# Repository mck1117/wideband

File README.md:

# rusEFI Wideband Controller

[User Documentation](https://rusefi.com/s/wb)

[Forum Thread](https://rusefi.com/forum/viewtopic.php?f=4&t=1856)

## Building Firmware

The `firmware/boards` directory contains configuration for each board this firmware supports.

For the standalone board and the module built in to rusEFI Hellen boards, `f0_module` is the correct target.  Use the `build_wideband.sh` script to build and package the wideband firmware: both a bin including the bootloader, and a header file consumed by rusEFI that contains no bootloader, to be uploaded over CAN (via the aforementioned bootloader).

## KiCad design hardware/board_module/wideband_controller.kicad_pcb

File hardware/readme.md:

* board_module
The main part of stm32f042 LSU 4.9 wideband.

* board_fw_tool
Initial USB DFU firmware programming fixture.

* board_carrier
Lower part of the sandwich.

* board_dev
Development version of above hardware.

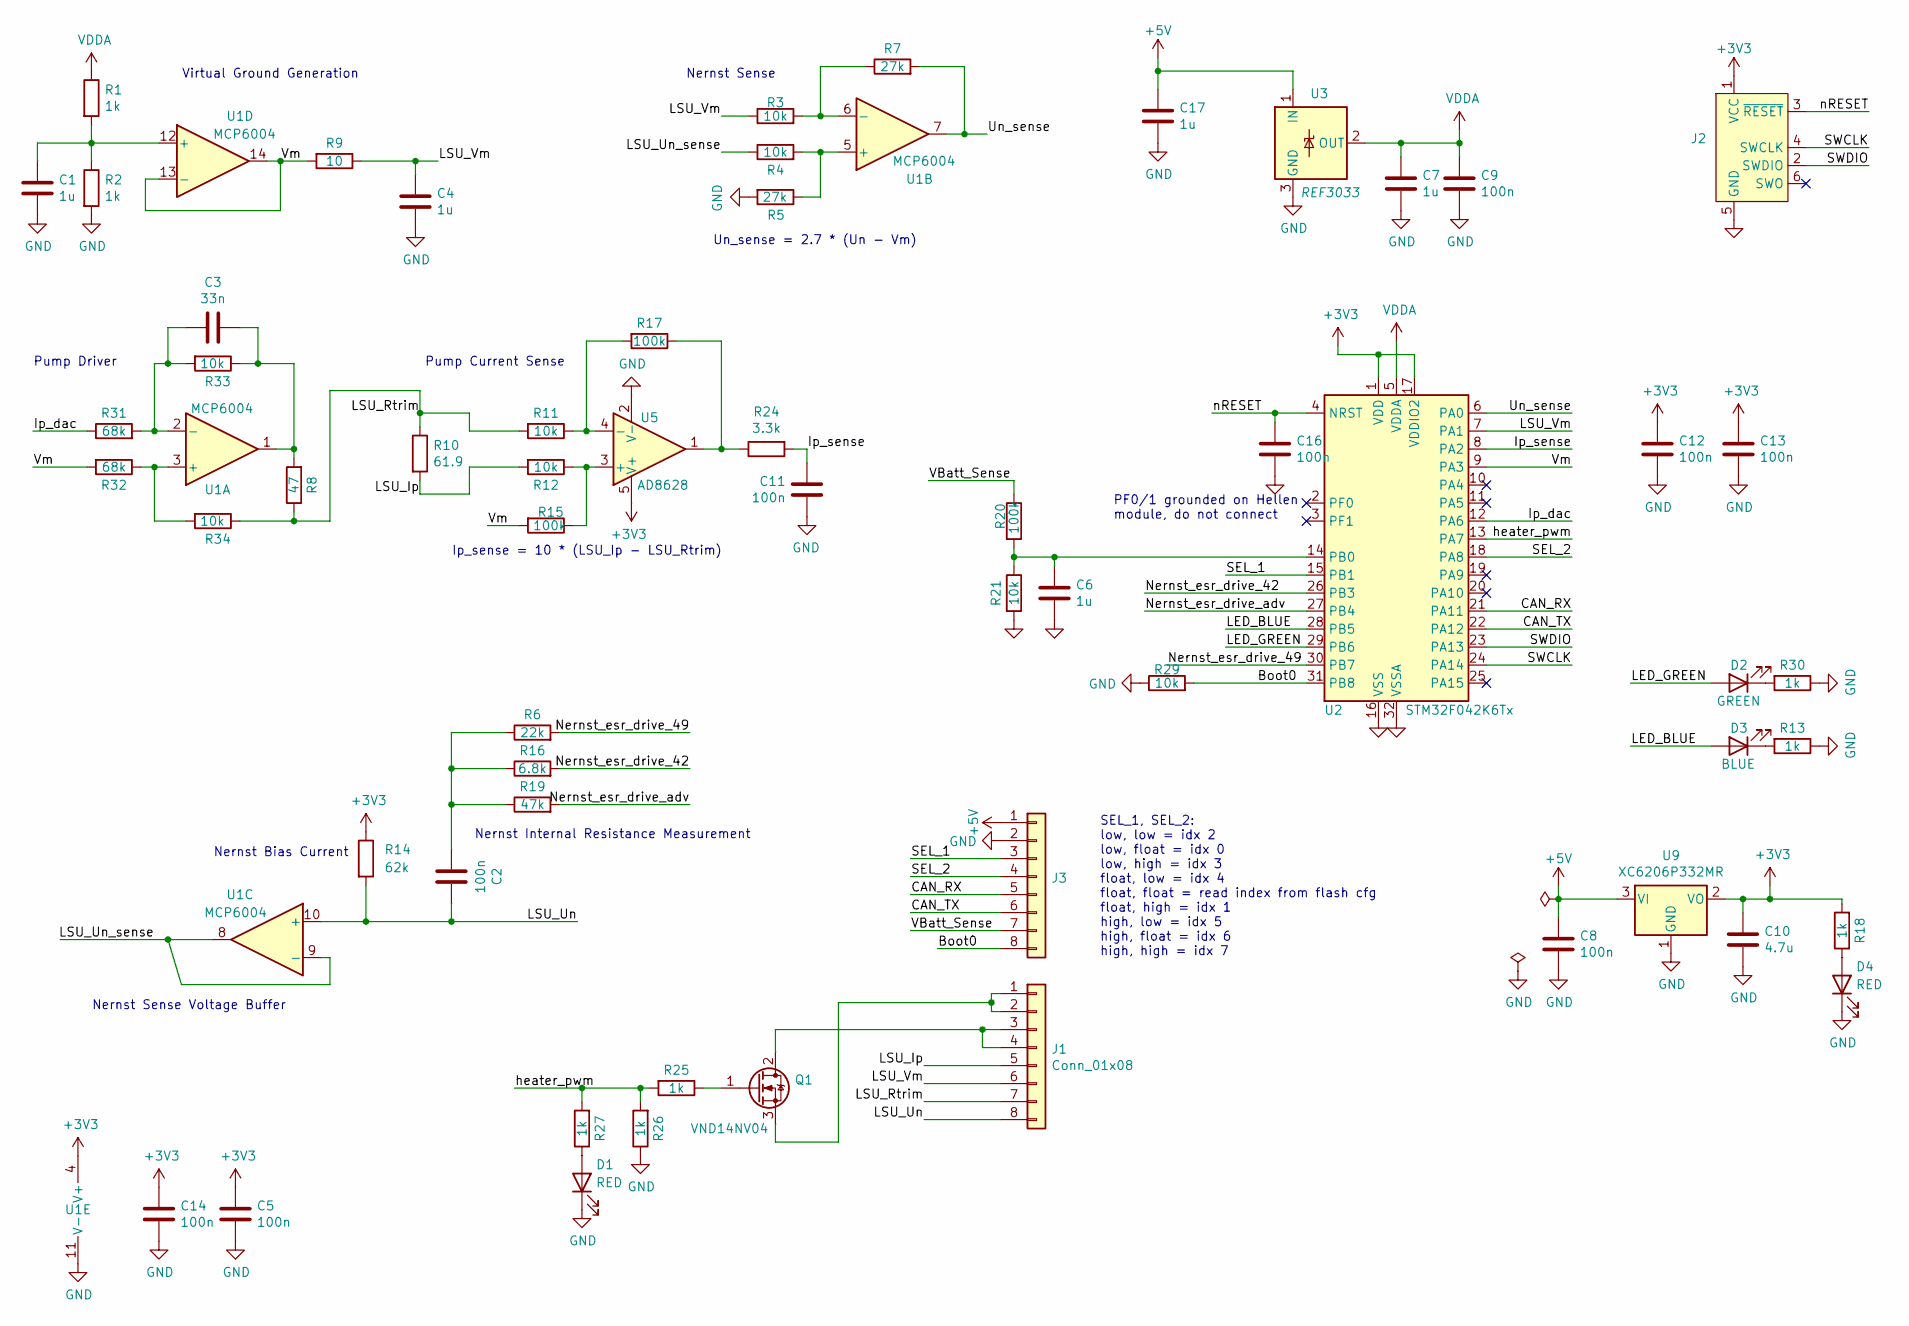
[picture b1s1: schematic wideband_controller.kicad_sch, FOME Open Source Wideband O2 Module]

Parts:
C1, C4, C6, C7, C17: 1u; C_0402_1005Metric; LCSC C52923
C2, C5, C8, C9, C11, C12, C13, C14, C16: 100n; C_0402_1005Metric; LCSC C1525
C3: 33n; C_0402_1005Metric; LCSC C1585
C10: 4.7u; C_0603_1608Metric; LCSC C19666
D1, D4: RED; LED_0603_1608Metric; LCSC C2286
D2: GREEN; LED_0603_1608Metric; LCSC C12624
D3: BLUE; LED_0603_1608Metric; LCSC C2288
J1, J3: Conn_01x08; PinHeader_1x08_P2.54mm_Vertical; LCSC C32713274
J2: Conn_ARM_SWD_TagConnect_TC2030; Tag-Connect_TC2030-IDC-NL_2x03_P1.27mm_Vertical
Q1: VND14NV04; TO-252-2; LCSC C2649436
R1, R2, R13, R18, R25, R26, R27, R30: 1k; R_0402_1005Metric; LCSC C11702
R3, R4, R11, R12, R21, R29, R33, R34: 10k; R_0402_1005Metric; LCSC C25744
R5, R7: 27k; R_0402_1005Metric; LCSC C25771
R6: 22k; R_0402_1005Metric; LCSC C25768
R8: 47; R_0402_1005Metric; LCSC C25118
R9: 10; R_0402_1005Metric; LCSC C25077
R10: 61.9; R_0603_1608Metric; LCSC C23092
R14: 62k; R_0603_1608Metric; LCSC C23221
R15, R17, R20: 100k; R_0402_1005Metric; LCSC C25741
R16: 6.8k; R_0402_1005Metric; LCSC C25917
R19: 47k; R_0402_1005Metric; LCSC C25792
R24: 3.3k; R_0402_1005Metric; LCSC C25890
R31, R32: 68k; R_0402_1005Metric; LCSC C36871
U1: MCP6004; TSSOP-14_4.4x5mm_P0.65mm; LCSC C50282
U2: STM32F042K6Tx; LQFP-32_7x7mm_P0.8mm; LCSC C69216
U3: REF3033; SOT-23; LCSC C36658
U5: AD8628; TSOT-23-5; LCSC C29309
U9: XC6206P332MR; SOT-23; LCSC C5446

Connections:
+3V3: C5.1, C10.1, C12.1, C13.1, C14.1, J2.1 (VCC), R14.1, R18.2, U1.4 (V+), U2.1 (VDD), U2.17 (VDDIO2), U5.5 (V+), U9.2 (VO)
+5V: C8.1, C17.1, J3.1, U3.1 (IN), U9.3 (VI)
/Boot0: J3.8, R29.2, U2.31 (PB8)
/CAN_RX: J3.5, U2.21 (PA11)
/CAN_TX: J3.6, U2.22 (PA12)
/Ip_dac: R31.1, U2.12 (PA6)
/Ip_sense: C11.1, R24.2, U2.8 (PA2)
/LED_BLUE: D3.2 (A), U2.28 (PB5)
/LED_GREEN: D2.2 (A), U2.29 (PB6)
/LSU_Ip: J1.5, R10.2, R12.2
/LSU_Rtrim: J1.7, R8.1, R10.1, R11.2, R34.1
/LSU_Un: C2.1, J1.8, R14.2, U1.10 (+)
/LSU_Un_sense: R4.1, U1.8, U1.9 (-)
/LSU_Vm: C4.1, J1.6, R3.1, R9.1, U2.7 (PA1)
/Nernst_esr_drive_42: R16.2, U2.26 (PB3)
/Nernst_esr_drive_49: R6.2, U2.30 (PB7)
/Nernst_esr_drive_adv: R19.2, U2.27 (PB4)
/SEL_1: J3.3, U2.15 (PB1)
/SEL_2: J3.4, U2.18 (PA8)
/SWCLK: J2.4 (SWCLK), U2.24 (PA14)
/SWDIO: J2.2 (SWDIO), U2.23 (PA13)
/Un_sense: R7.2, U1.7, U2.6 (PA0)
/VBatt_Sense: J3.7, R20.1
/Vm: R9.2, R15.2, R32.2, U1.13 (-), U1.14, U2.9 (PA3)
/heater_pwm: R25.2, R26.2, R27.2, U2.13 (PA7)
/nRESET: C16.1, J2.3 (~RESET), U2.4 (NRST)
GND: C1.2, C4.2, C5.2, C6.2, C7.2, C8.2, C9.2, C10.2, C11.2, C12.2, C13.2, C14.2, C16.2, C17.2, D1.1 (K), D4.1 (K), J2.5 (GND), J3.2, R2.2, R5.2, R13.1, R21.2, R26.1, R29.1, R30.1, U1.11 (V-), U2.16 (VSS), U2.32 (VSSA), U3.3 (GND), U5.2 (V-), U9.1 (GND)
unnamed: C2.2, R6.1, R16.1, R19.1
unnamed: C3.1, R8.2, R33.1, U1.1
unnamed: D1.2 (A), R27.1
unnamed: D2.1 (K), R30.2
unnamed: D3.1 (K), R13.2
unnamed: D4.2 (A), R18.1
unnamed: J1.1, J1.2, Q1.3 (S)
unnamed: J1.3, J1.4, Q1.2 (D)
unnamed: Q1.1 (G), R25.1
unnamed: R17.1, R24.1, U5.1
unnamed: R32.1, R34.2, U1.3 (+)
unnamed: C3.2, R31.2, R33.2, U1.2 (-)
unnamed: R4.2, R5.1, U1.5 (+)
unnamed: R3.2, R7.1, U1.6 (-)
unnamed: C1.1, R1.2, R2.1, U1.12 (+)
unnamed: C6.1, R20.2, R21.1, U2.14 (PB0)
unnamed: R12.1, R15.1, U5.3 (+)
unnamed: R11.1, R17.2, U5.4 (-)
VDDA: C7.1, C9.1, R1.1, U2.5 (VDDA), U3.2 (OUT)

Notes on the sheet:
Un_sense = 2.7 * (Un - Vm)
Nernst Internal Resistance Measurement
Pump Driver
Nernst Sense Voltage Buffer
PF0/1 grounded on Hellen module, do not connect
Nernst Bias Current
Ip_sense = 10 * (LSU_Ip - LSU_Rtrim)
Virtual Ground Generation
Nernst Sense
Pump Current Sense
SEL_1, SEL_2: low, low = idx 2 low, float = idx 0 low, high = idx 3 float, low = idx 4 float, float = read index from flash cfg float, high = idx 1 high, low = idx 5 high, float = idx 6 high, high = idx 7

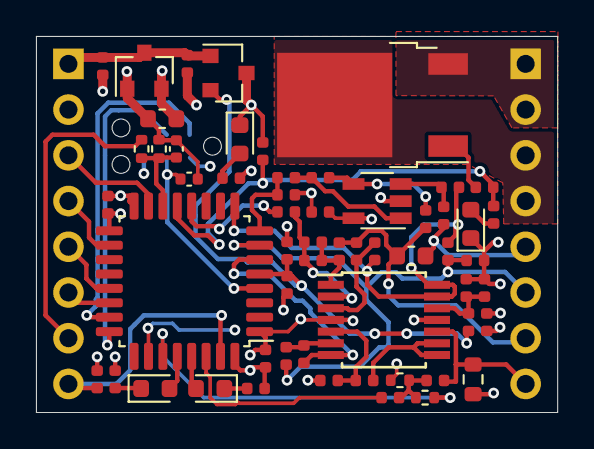
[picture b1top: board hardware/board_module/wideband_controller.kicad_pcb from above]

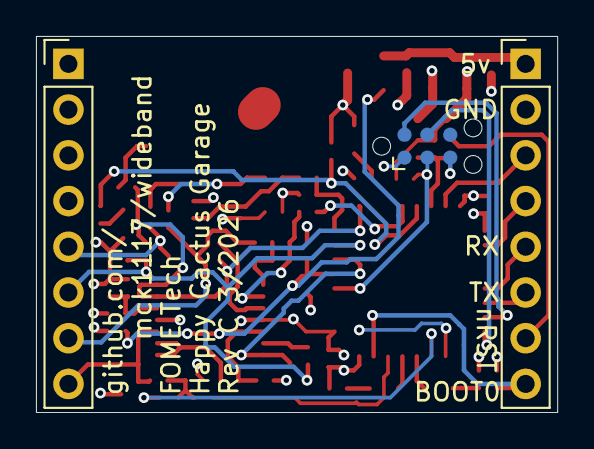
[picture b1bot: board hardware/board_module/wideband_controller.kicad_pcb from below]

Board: 4 copper layers, 29.0 x 20.9 mm, 60 parts (3 on the bottom side), 46 nets.

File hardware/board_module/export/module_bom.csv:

Comment,Designator,Footprint, LCSC
1u,"C1,C4,C7",Capacitor_SMD:C_0402_1005Metric,C52923
4.7u,C10,Capacitor_SMD:C_0603_1608Metric,C19666
100n,"C2,C8,C9,C11,C13,C12,C14,C5",Capacitor_SMD:C_0402_1005Metric,C1525
33n,C3,Capacitor_SMD:C_0402_1005Metric,C1585
DNP,"C6,C15",Capacitor_SMD:C_0402_1005Metric,
RED,"D1,D4",LED_SMD:LED_0603_1608Metric,C2286
GREEN,D2,LED_SMD:LED_0603_1608Metric,C72043
BLUE,D3,LED_SMD:LED_0603_1608Metric,C72041
BTS3028,Q1,Package_TO_SOT_SMD:TO-252-2,C112639
61.9,R10,Resistor_SMD:R_0603_1608Metric,C23092
100k,"R15,R17",Resistor_SMD:R_0402_1005Metric,C25741
10k,"R2,R11,R12,R4,R3,R1,R33,R34,R29",Resistor_SMD:R_0402_1005Metric,C25744
20k,"R22,R14,R16",Resistor_SMD:R_0402_1005Metric,C25765
33,R23,Resistor_SMD:R_0402_1005Metric,C25105
3.3k,R24,Resistor_SMD:R_0402_1005Metric,C25890
1k,"R25,R26,R27,R30,R13,R18",Resistor_SMD:R_0402_1005Metric,C11702
68k,"R32,R31",Resistor_SMD:R_0402_1005Metric,C36871
22k,R6,Resistor_SMD:R_0402_1005Metric,C25768
27k,"R7,R5",Resistor_SMD:R_0402_1005Metric,C25771
47,R8,Resistor_SMD:R_0402_1005Metric,C25118
10,R9,Resistor_SMD:R_0402_1005Metric,C25077
MCP6004,U1,Package_SO:TSSOP-14_4.4x5mm_P0.65mm,C50282
STM32F042K6Tx,U2,Package_QFP:LQFP-32_7x7mm_P0.8mm,C69216
AD8628,U5,Package_TO_SOT_SMD:TSOT-23-5,C29309
XC6206P332MR,U9,Package_TO_SOT_SMD:SOT-23,C5446

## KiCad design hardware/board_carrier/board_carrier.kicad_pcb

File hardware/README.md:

## `board_module`

Wideband O2 sensor controller on a postage stamp. Contains all the analog and digital control logic to handle a Bosch LSU 4.2, 4.9, or ADV sensor.

Intended to either be mounted on an ECU as a module, or on `board_carrier` to run standalone.

## `board_carrier`

Stacks under `board_module`, has 5v regulator, CAN tranceiver, etc so that the module can exist standlone.

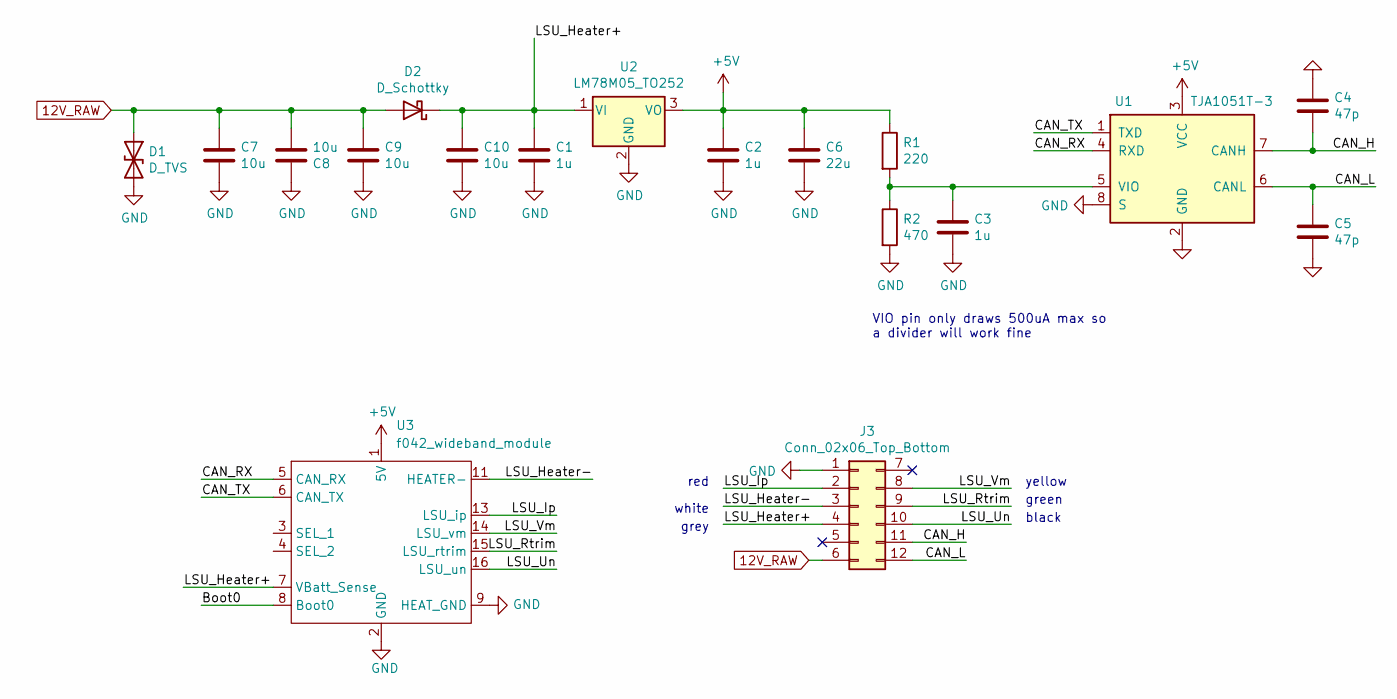
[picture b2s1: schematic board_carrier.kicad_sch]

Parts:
C1, C2, C3: 1u; C_0603_1608Metric; LCSC C15849
C4, C5: 47p; C_0402_1005Metric; LCSC C1567
C6: 22u; C_0805_2012Metric; LCSC C45783
C7, C8, C9, C10: 10u; C_1206_3216Metric; LCSC C13585
D1: D_TVS; D_SMC; LCSC C151279
D2: D_Schottky; D_SMA; LCSC C22452
J3: Conn_02x06_Top_Bottom; mx120g-12
R1: 220; R_0603_1608Metric; LCSC C22962
R2: 470; R_0603_1608Metric; LCSC C23179
U1: TJA1051T-3; SOIC-8_3.9x4.9mm_P1.27mm; LCSC C38695
U2: LM78M05_TO252; TO-252-2; LCSC C58069
U3: f042_wideband_module

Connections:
12V_RAW: C7.1, C8.2, C9.1, D1.1 (A1), D2.2 (A), J3.6
+5V: C2.1, C6.1, R1.1, U1.3 (VCC), U2.3 (VO), U3.1 (5V)
/Boot0: U3.8 (Boot0)
/CAN_H: C4.2, J3.11, U1.7 (CANH)
/CAN_L: C5.1, J3.12, U1.6 (CANL)
/CAN_RX: U1.4 (RXD), U3.5 (CAN_RX)
/CAN_TX: U1.1 (TXD), U3.6 (CAN_TX)
/LSU_Heater+: C1.1, C10.1, D2.1 (K), J3.4, U2.1 (VI), U3.7 (VBatt_Sense)
/LSU_Heater-: J3.3, U3.11 (HEATER-), U3.12 (HEATER-)
/LSU_Ip: J3.2, U3.13 (LSU_ip)
/LSU_Rtrim: J3.9, U3.15 (LSU_rtrim)
/LSU_Un: J3.10, U3.16 (LSU_un)
/LSU_Vm: J3.8, U3.14 (LSU_vm)
GND: C1.2, C2.2, C3.2, C4.1, C5.2, C6.2, C7.2, C8.1, C9.2, C10.2, D1.2 (A2), J3.1, R2.2, U1.2 (GND), U1.8 (S), U2.2 (GND), U3.2 (GND), U3.9 (HEAT_GND), U3.10 (HEAT_GND2)
unnamed: C3.1, R1.2, R2.1, U1.5 (VIO)

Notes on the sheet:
yellow
green
red
black
white
VIO pin only draws 500uA max so a divider will work fine
grey

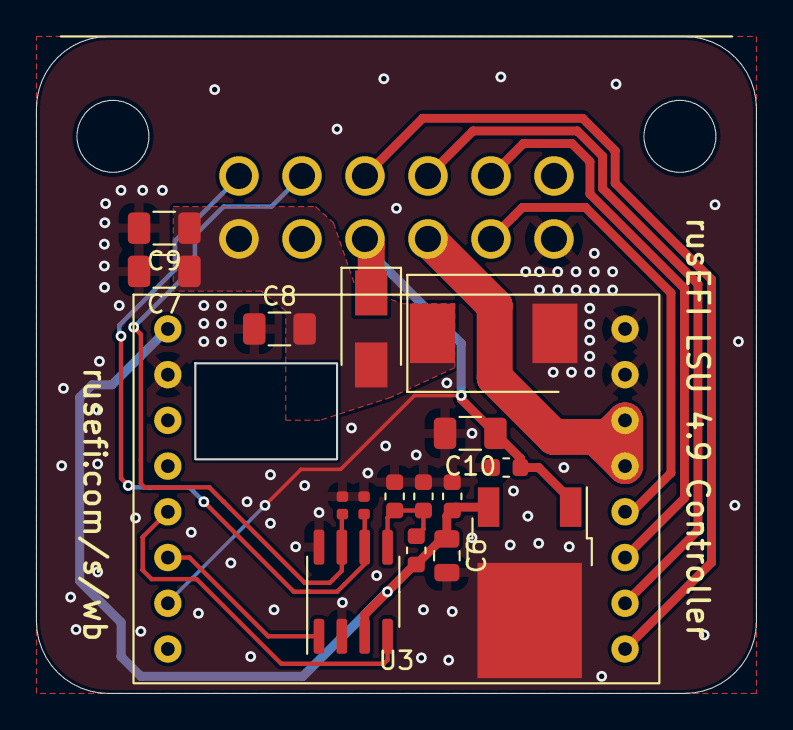
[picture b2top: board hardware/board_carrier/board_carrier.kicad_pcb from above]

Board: 2 copper layers, 39.9 x 36.4 mm, 18 parts (0 on the bottom side), 14 nets.

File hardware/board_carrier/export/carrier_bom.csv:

Comment,Designator,Footprint, LCSC
1u,"C1,C2,C3",Capacitor_SMD:C_0603_1608Metric,C15849
47p,"C4,C5",Capacitor_SMD:C_0402_1005Metric,C1567
D_TVS,D1,Diode_SMD:D_SMC,C133648
D_Schottky,D2,Diode_SMD:D_SMA,C8678
220,R1,Resistor_SMD:R_0603_1608Metric,C22962
470,R2,Resistor_SMD:R_0603_1608Metric,C23179
TJA1051T-3,U1,Package_SO:SOIC-8_3.9x4.9mm_P1.27mm,C38695
LM78M05_TO252,U2,Package_TO_SOT_SMD:TO-252-2,C58069

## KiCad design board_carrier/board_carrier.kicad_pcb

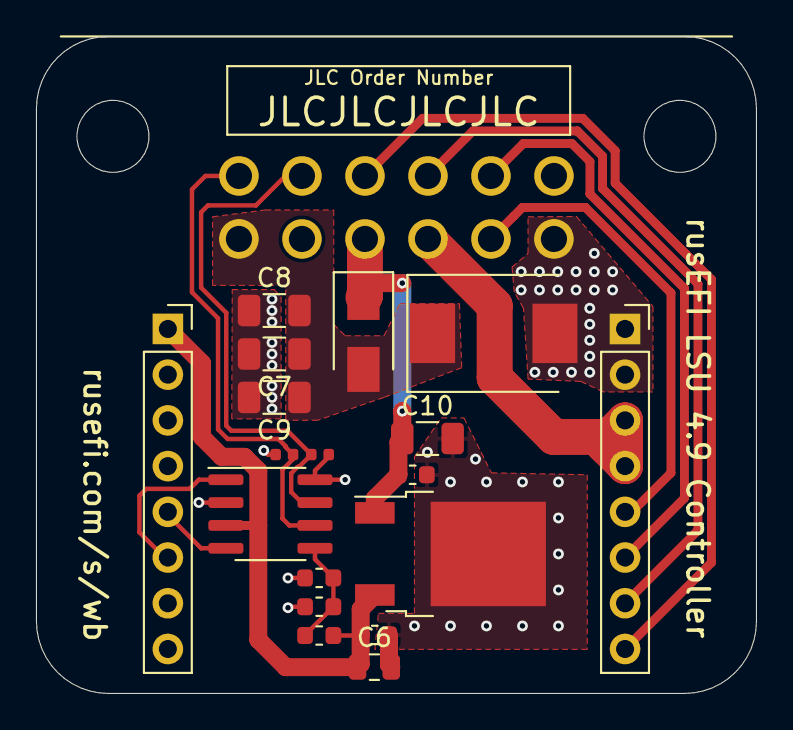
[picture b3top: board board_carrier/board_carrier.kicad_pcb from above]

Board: 2 copper layers, 40.0 x 36.5 mm, 20 parts (0 on the bottom side), 14 nets.

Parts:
C1, C2, C3: 1u; C_0603_1608Metric
C4, C5: 47p; C_0402_1005Metric
C6: 22u; C_0805_2012Metric
C7, C8, C9, C10: 10u; C_1206_3216Metric
D1: D_TVS; D_SMC
D2: D_Schottky; D_SMA
J1, J2: Conn_01x08; PinSocket_1x08_P2.54mm_Vertical
J3: Conn_02x06_Top_Bottom; mx120g-12
JLCTAG**: JLC_PCB_TAG
R1: 220; R_0603_1608Metric
R2: 470; R_0603_1608Metric
U1: TJA1051T-3; SOIC-8_3.9x4.9mm_P1.27mm
U2: LM78M05_TO252; TO-252-2

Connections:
12V_RAW: C7.1, C8.2, C9.1, D1.1, D2.2, J3.6
+5V: C2.1, C6.1, J1.1, R1.1, U1.3, U2.3
/CAN_H: C4.2, J3.11, U1.7
/CAN_L: C5.1, J3.12, U1.6
/CAN_RX: J1.5, U1.4
/CAN_TX: J1.6, U1.1
/LSU_Heater+: C1.1, C10.1, D2.1, J3.4, U2.1
/LSU_Heater-: J2.3, J2.4, J3.3
/LSU_Ip: J2.5, J3.2
/LSU_Rtrim: J2.7, J3.9
/LSU_Un: J2.8, J3.10
/LSU_Vm: J2.6, J3.8
GND: C1.2, C2.2, C3.2, C4.1, C5.2, C6.2, C7.2, C8.1, C9.2, C10.2, D1.2, J1.2, J2.1, J2.2, J3.1, R2.2, U1.2, U1.8, U2.2
unnamed: C3.1, R1.2, R2.1, U1.5

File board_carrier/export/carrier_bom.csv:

Comment,Designator,Footprint, LCSC
1u,"C1,C2,C3",Capacitor_SMD:C_0603_1608Metric,C15849
D_TVS,D1,Diode_SMD:D_SMC,C133648
D_Schottky,D2,Diode_SMD:D_SMA,C8678
220,R1,Resistor_SMD:R_0603_1608Metric,C22962
470,R2,Resistor_SMD:R_0603_1608Metric,C23179
TJA1051T-3,U1,Package_SO:SOIC-8_3.9x4.9mm_P1.27mm,C38695
LM78M05_TO252,U2,Package_TO_SOT_SMD:TO-252-2,C58069

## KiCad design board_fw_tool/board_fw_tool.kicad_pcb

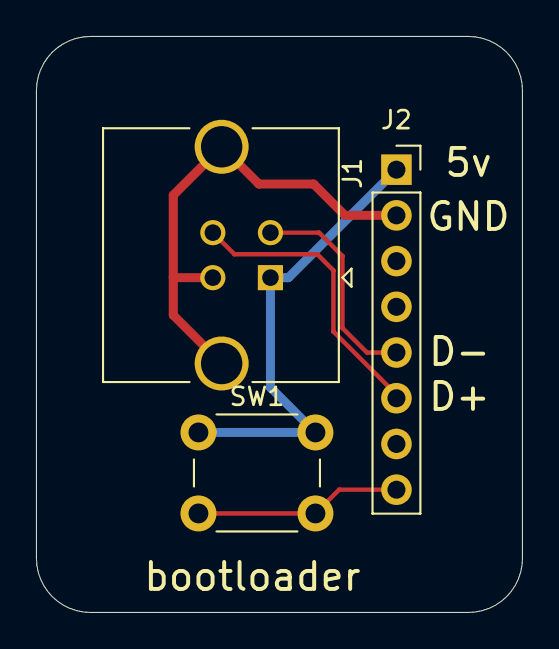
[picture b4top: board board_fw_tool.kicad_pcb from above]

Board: 2 copper layers, 27.0 x 32.0 mm, 3 parts (0 on the bottom side), 5 nets.

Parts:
J1: USB_B; USB_B_TE_5787834_Vertical
J2: Conn_01x08; PinSocket_1x08_P2.54mm_Vertical
SW1: SW_Push; SW_PUSH_6mm

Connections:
GND: J1.4, J1.5, J2.2
unnamed: J1.1, J2.1, SW1.1
unnamed: J1.2, J2.5
unnamed: J1.3, J2.6
unnamed: J2.8, SW1.2

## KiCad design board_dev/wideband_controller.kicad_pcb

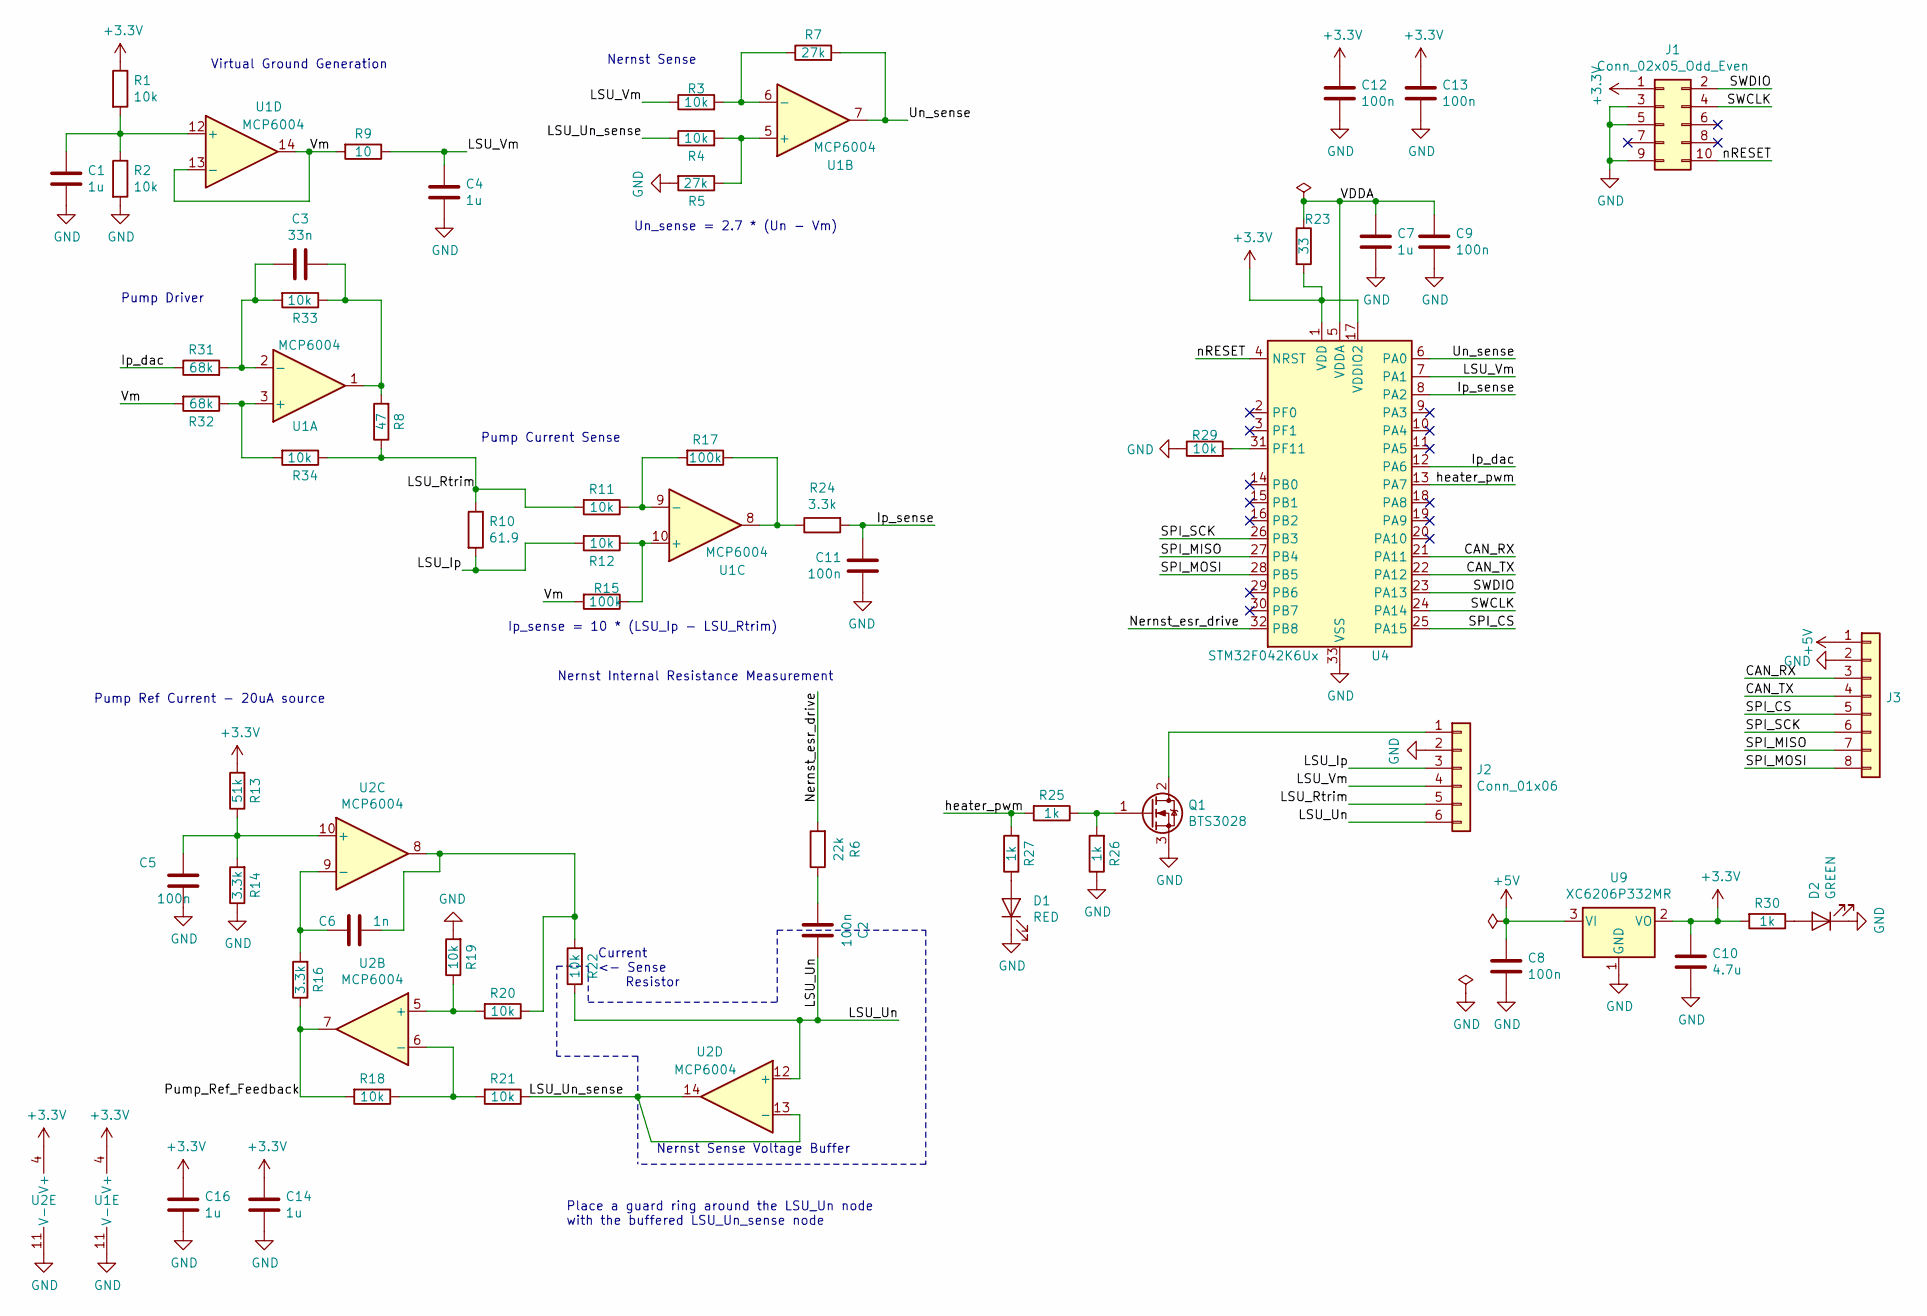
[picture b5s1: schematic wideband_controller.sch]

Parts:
C1, C4, C7, C14, C16: 1u; C_0402_1005Metric; LCSC C52923
C2: 100n; C_0603_1608Metric; LCSC C14663
C3: 33n; C_0402_1005Metric; LCSC C1585
C5, C8, C9, C11, C12, C13: 100n; C_0402_1005Metric; LCSC C1525
C6: 1n; C_0402_1005Metric; LCSC C1523
C10: 4.7u; C_0603_1608Metric; LCSC C19666
D1: RED; LED_0603_1608Metric; LCSC C2286
D2: GREEN; LED_0603_1608Metric; LCSC C72043
J1: Conn_02x05_Odd_Even; PinHeader_2x05_P1.27mm_Vertical_SMD
J2: Conn_01x06; PhoenixContact_MSTBVA_2,5_6-G-5,08_1x06_P5.08mm_Vertical
J3: Conn_01x08; PinHeader_1x08_P2.54mm_Vertical
Q1: BTS3028; TO-252-2; LCSC C112639
R1, R2, R3, R4, R11, R12, R18, R19, R20, R21, R29, R33, R34: 10k; R_0402_1005Metric; LCSC C25744
R5, R7: 27k; R_0402_1005Metric; LCSC C25771
R6: 22k; R_0402_1005Metric; LCSC C25768
R8: 47; R_0402_1005Metric; LCSC C25118
R9: 10; R_0402_1005Metric; LCSC C25077
R10: 61.9; R_0603_1608Metric; LCSC C23092
R13: 51k; R_0402_1005Metric; LCSC C25794
R14, R16, R24: 3.3k; R_0402_1005Metric; LCSC C25890
R15, R17: 100k; R_0402_1005Metric; LCSC C25741
R22: 10k; R_0603_1608Metric; LCSC C25804
R23: 33; R_0402_1005Metric; LCSC C25105
R25, R26, R27, R30: 1k; R_0402_1005Metric; LCSC C11702
R31, R32: 68k; R_0402_1005Metric; LCSC C36871
U1, U2: MCP6004; TSSOP-14_4.4x5mm_P0.65mm; LCSC C50282
U4: STM32F042K6Ux; QFN-32-1EP_5x5mm_P0.5mm_EP3.45x3.45mm; LCSC C110616
U9: XC6206P332MR; SOT-23; LCSC C5446

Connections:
+3V3: C10.1, C12.1, C13.1, C14.1, C16.1, J1.1, R1.1, R13.2, R23.2, R30.2, U1.4 (V+), U2.4 (V+), U4.1 (VDD), U4.17 (VDDIO2), U9.2 (VO)
+5V: C8.1, J3.1, U9.3 (VI)
/CAN_RX: J3.3, U4.21 (PA11)
/CAN_TX: J3.4, U4.22 (PA12)
/Ip_dac: R31.1, U4.12 (PA6)
/Ip_sense: C11.1, R24.2, U4.8 (PA2)
/LSU_Ip: J2.3, R10.2, R12.2
/LSU_Rtrim: J2.5, R8.1, R10.1, R11.2, R34.1
/LSU_Un: C2.1, J2.6, R22.1, U2.12 (+)
/LSU_Un_sense: R4.1, R21.1, U2.13 (-), U2.14
/LSU_Vm: C4.1, J2.4, R3.1, R9.1, U4.7 (PA1)
/Nernst_esr_drive: R6.2, U4.32 (PB8)
/Pump_Ref_Feedback: R16.1, R18.2, U2.7
/SPI_CS: J3.5, U4.25 (PA15)
/SPI_MISO: J3.7, U4.27 (PB4)
/SPI_MOSI: J3.8, U4.28 (PB5)
/SPI_SCK: J3.6, U4.26 (PB3)
/SWCLK: J1.4, U4.24 (PA14)
/SWDIO: J1.2, U4.23 (PA13)
/Un_sense: R7.2, U1.7, U4.6 (PA0)
/VDDA: C7.1, C9.1, R23.1, U4.5 (VDDA)
/Vm: R9.2, R15.2, R32.2, U1.13 (-), U1.14
/heater_pwm: R25.2, R27.2, U4.13 (PA7)
/nRESET: J1.10, U4.4 (NRST)
GND: C1.2, C4.2, C5.2, C7.2, C8.2, C9.2, C10.2, C11.2, C12.2, C13.2, C14.2, C16.2, D1.1 (K), D2.1 (K), J1.3, J1.5, J1.9, J2.2, J3.2, Q1.3 (S), R2.2, R5.2, R14.1, R19.2, R26.1, R29.1, U1.11 (V-), U2.11 (V-), U4.33 (VSS), U9.1 (GND)
unnamed: C1.1, R1.2, R2.1, U1.12 (+)
unnamed: C2.2, R6.1
unnamed: C3.1, R8.2, R33.1, U1.1
unnamed: C3.2, R31.2, R33.2, U1.2 (-)
unnamed: C5.1, R13.1, R14.2, U2.10 (+)
unnamed: C6.1, R20.1, R22.2, U2.8
unnamed: C6.2, R16.2, U2.9 (-)
unnamed: D1.2 (A), R27.1
unnamed: D2.2 (A), R30.1
unnamed: J2.1, Q1.2 (D)
unnamed: Q1.1 (G), R25.1, R26.2
unnamed: R3.2, R7.1, U1.6 (-)
unnamed: R4.2, R5.1, U1.5 (+)
unnamed: R11.1, R17.2, U1.9 (-)
unnamed: R12.1, R15.1, U1.10 (+)
unnamed: R17.1, R24.1, U1.8
unnamed: R18.1, R21.2, U2.6 (-)
unnamed: R19.1, R20.2, U2.5 (+)
unnamed: R29.2, U4.31 (PF11)
unnamed: R32.1, R34.2, U1.3 (+)

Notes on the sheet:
Pump Current Sense
Virtual Ground Generation
Nernst Internal Resistance Measurement
Pump Ref Current - 20uA source
Pump Driver
Nernst Sense
Un_sense = 2.7 * (Un - Vm)
Ip_sense = 10 * (LSU_Ip - LSU_Rtrim)
Nernst Sense Voltage Buffer
Current <- Sense Resistor
Place a guard ring around the LSU_Un node with the buffered LSU_Un_sense node

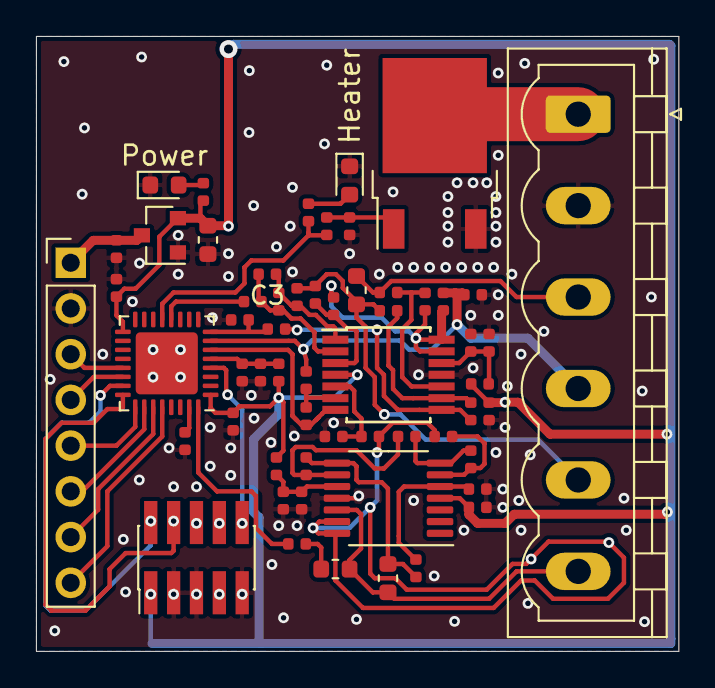
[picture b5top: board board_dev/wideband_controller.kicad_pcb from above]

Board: 2 copper layers, 35.7 x 34.2 mm, 58 parts (0 on the bottom side), 45 nets.

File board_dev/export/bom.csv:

Comment,Designator,Footprint, LCSC
1u,"C1,C4,C7,C14,C16",Capacitor_SMD:C_0402_1005Metric,C52923
4.7u,C10,Capacitor_SMD:C_0603_1608Metric,C19666
100n,C2,Capacitor_SMD:C_0603_1608Metric,C14663
33n,C3,Capacitor_SMD:C_0402_1005Metric,C1585
1n,C6,Capacitor_SMD:C_0402_1005Metric,C1523
100n,"C8,C5,C9,C11,C13,C12",Capacitor_SMD:C_0402_1005Metric,C1525
RED,D1,LED_SMD:LED_0603_1608Metric,C2286
GREEN,D2,LED_SMD:LED_0603_1608Metric,C72043
Conn_02x05_Odd_Even,J1,Connector_PinHeader_1.27mm:PinHeader_2x05_P1.27mm_Vertical_SMD,
Conn_01x06,J2,"Connector_Phoenix_MSTB:PhoenixContact_MSTBVA_2,5_6-G-5,08_1x06_P5.08mm_Vertical",
Conn_01x08,J3,Connector_PinHeader_2.54mm:PinHeader_1x08_P2.54mm_Vertical,
BTS3028,Q1,Package_TO_SOT_SMD:TO-252-2,C112639
61.9,R10,Resistor_SMD:R_0603_1608Metric,C23092
51k,R13,Resistor_SMD:R_0402_1005Metric,C25794
3.3k,"R14,R16,R24",Resistor_SMD:R_0402_1005Metric,C25890
100k,"R15,R17",Resistor_SMD:R_0402_1005Metric,C25741
10k,"R2,R11,R12,R4,R3,R18,R21,R20,R19,R29,R1,R33,R34",Resistor_SMD:R_0402_1005Metric,C25744
10k,R22,Resistor_SMD:R_0603_1608Metric,C25804
33,R23,Resistor_SMD:R_0402_1005Metric,C25105
1k,"R25,R26,R27,R30",Resistor_SMD:R_0402_1005Metric,C11702
68k,"R32,R31",Resistor_SMD:R_0402_1005Metric,C36871
22k,R6,Resistor_SMD:R_0402_1005Metric,C25768
27k,"R7,R5",Resistor_SMD:R_0402_1005Metric,C25771
47,R8,Resistor_SMD:R_0402_1005Metric,C25118
10,R9,Resistor_SMD:R_0402_1005Metric,C25077
MCP6004,"U1,U2",Package_SO:TSSOP-14_4.4x5mm_P0.65mm,C50282
STM32F042K6Ux,U4,Package_DFN_QFN:QFN-32-1EP_5x5mm_P0.5mm_EP3.45x3.45mm,C110616
XC6206P332MR,U9,Package_TO_SOT_SMD:SOT-23,C5446

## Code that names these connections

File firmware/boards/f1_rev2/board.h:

/*
    ChibiOS - Copyright (C) 2006..2018 Giovanni Di Sirio

    Licensed under the Apache License, Version 2.0 (the "License");
    you may not use this file except in compliance with the License.
    You may obtain a copy of the License at

        http://www.apache.org/licenses/LICENSE-2.0

    Unless required by applicable law or agreed to in writing, software
    distributed under the License is distributed on an "AS IS" BASIS,
    WITHOUT WARRANTIES OR CONDITIONS OF ANY KIND, either express or implied.
    See the License for the specific language governing permissions and
    limitations under the License.
*/

#ifndef _BOARD_H_
#define _BOARD_H_

/*
 * Board identifier.
 */
#define BOARD_RUSEFI_WIDEBAND_REV2
/*
 * Board identifier.
 */
#define BOARD_NAME                  "rusEfi Wideband Controller rev 2"

/*
 * Board oscillators-related settings.
 * NOTE: LSE not fitted.
 * NOTE: HSE not fitted.
 */
#if !defined(STM32_LSECLK)
#define STM32_LSECLK                0U
#endif

#if !defined(STM32_HSECLK)
#define STM32_HSECLK                0U
#endif

/*
 * MCU type, supported types are defined in ./os/hal/platforms/hal_lld.h.
 */
#define STM32F103xB

/*
 * IO pins assignments.
 */

/*
 * I/O ports initial setup, this configuration is established soon after reset
 * in the initialization code.
 *
 * The digits have the following meaning:
 *   0 - Analog input.
 *   1 - Push Pull output 10MHz.
 *   2 - Push Pull output 2MHz.
 *   3 - Push Pull output 50MHz.
 *   4 - Digital input.
 *   5 - Open Drain output 10MHz.
 *   6 - Open Drain output 2MHz.
 *   7 - Open Drain output 50MHz.
 *   8 - Digital input with PullUp or PullDown resistor depending on ODR.
 *   9 - Alternate Push Pull output 10MHz.
 *   A - Alternate Push Pull output 2MHz.
 *   B - Alternate Push Pull output 50MHz.
 *   C - Reserved.
 *   D - Alternate Open Drain output 10MHz.
 *   E - Alternate Open Drain output 2MHz.
 *   F - Alternate Open Drain output 50MHz.
 * Please refer to the STM32 Reference Manual for details.
 */

/*
 * Port A setup.
 * PA0  - Vm_sense                  (analog in).
 * PA1  - Ip_dac (PWM)              (output pushpull, alternate, 2 MHz).
 * PA2  - unused (TP5)              (analog in).
 * PA3  - unused (TP3)              (analog in).
 * PA4  - unused (TP4)              (analog in).
 * PA5  - Un_sense                  (analog in).
 * PA6  - Ip_sense                  (analog in).
 * PA7  - Un_3x_sense               (analog in).
 * PA8  - LED_GREEN                 (output pushpull, 2 MHz).
 * PA9  - UART_TX                   (output pushpull, alternate, 50 Mhz).
 * PA10 - UART_RX                   (digital input, alternate).
 * PA11 - CAN_RX                    (digital input, alternate).
 * PA12 - CAN_TX                    (output pushpull, alternate, 50 Mhz).
 * PA13 - SWDIO                     (digital input)
 * PA14 - SWCLK                     (digital input)
 * PA15 - DISP0 - unused
 */
#define VAL_GPIOACRL            0x000000B0      /*  PA7...PA0 */
#define VAL_GPIOACRH            0x888B88B2      /* PA15...PA8 */
#define VAL_GPIOAODR            0x0000FFFF

/*
 * Port B setup.
 * PB0  - Vbatt_sense               (analog in).
 * PB1  - Heater_sense              (analog in).
 * PB2  - Nernsr_4.9_bias           (digital input, no pull) - keep high-Z after power on
 * PB3  - SWO                       (digital input)
 * PB4..PB5 - DISP1..DISP2 - unused
 * PB6  - heater_pwm                (output pushpull, alternate, 2 MHz).
 * PB7..PB9 - DISP4..DISP6 - unused
 * PB10 - Nernsr_ADV_esr_drive      (digital input, no pull) - keep high-Z after power on
 * PB11 - Nernsr_4.9_esr_drive      (digital input, no pull) - keep high-Z after power on
 * PB12 - Nernsr_4.2_esr_drive      (digital input, no pull) - keep high-Z after power on
 * PB13 - Blue LED                  (output pushpull, 2 MHz)
 * PB14 - PWMout2                   (output pushpull, alternate, 2 Mhz).
 * PB15 - PWMout1                   (output pushpull, alternate, 2 Mhz).
 */
#define VAL_GPIOBCRL            0x8A888400      /*  PB7...PB0 */
#define VAL_GPIOBCRH            0xAA244488      /* PB15...PB8 */
#define VAL_GPIOBODR            0x0000FFFF

/*
 * Port C setup. (only PC13..PC15 exist on 48-pin package)
 * PC13 - config0                   (digital input, no pull)
 * PC14 - config1                   (digital input, no pull)
 * PC15 - not used                  (digital input, pull-up)
 */
#define VAL_GPIOCCRL            0x88888888      /*  PC7...PC0 */
#define VAL_GPIOCCRH            0x84488888      /* PC15...PC8 */
#define VAL_GPIOCODR            0x0000FFFF

/*
 * Port D setup.
 * Everything input with pull-up except:
 */
#define VAL_GPIODCRL            0x88888888      /*  PD7...PD0 */
#define VAL_GPIODCRH            0x88888888      /* PD15...PD8 */
#define VAL_GPIODODR            0x0000FFFF

/*
 * Port E setup.
 * Everything input with pull-up except:
 */
#define VAL_GPIOECRL            0x88888888      /*  PE7...PE0 */
#define VAL_GPIOECRH            0x88888888      /* PE15...PE8 */
#define VAL_GPIOEODR            0x0000FFFF

/*
 * USB bus activation macro, required by the USB driver.
 */
#define usb_lld_connect_bus(usbp)

/*
 * USB bus de-activation macro, required by the USB driver.
 */
#define usb_lld_disconnect_bus(usbp)

#if !defined(_FROM_ASM_)
#ifdef __cplusplus
extern "C" {
#endif
  void boardInit(void);
#ifdef __cplusplus
}
#endif
#endif /* _FROM_ASM_ */

#endif /* _BOARD_H_ */

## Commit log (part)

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2023-04-26 dac: fix overflow
2023-04-26 dac: fix overflow (#238)
2023-04-27 better file name to facilitate upload/download for instance see https://rusefi.com/online/ini/rusefi/2023/04/21/
2023-04-27 doc (#233)
2023-04-27 doc (#237)
2023-04-27 auxout: designated initializers (#230)
    (cherry picked from commit d458a094b64de13e8a1540dc0fb4facade6b332f)
2023-04-27 better file name to facilitate upload/download (#240)
    for instance see https://rusefi.com/online/ini/rusefi/2023/04/21/
2023-04-27 f1_dual_rev1: disable unused TIM1, TIM2
    (cherry picked from commit 9e71c3813fd09c080c0eb2f1e63fe82b475efb4f)
2023-04-27 f1_dual_rev1: fix can timings
    (cherry picked from commit 6437b3d92047adefe6534efaa57062bdda449d37)
2023-04-27 f1_dual_rev1: add CAN timings for 125L, 250K and 1Mbps
    (cherry picked from commit bc988d10dda43bfc8b4566de274e3b99bc6b8a5e)
2023-04-27 fix pwm definitions
    (cherry picked from commit ce9e69b997290bbd7abcfe5af2926b1d556070cf)
2023-04-27 auxout: some boards use primary PWM outputs instead of complementary
    (cherry picked from commit c13b95441e7b284a36445c261199e96580e94ebd)
2023-04-27 auxout: implement ripple cancelation using inverted PWM
    (cherry picked from commit 77cbc04990421b24021639b098ea6040af3a12f8)
2023-04-27 Dual 1 (#241)
    * f1_dual_rev1: add pinmux settings for port F and G
    To supress compiler warning.
    (cherry picked from commit 89876fe8eaad933308b63a4b0b1666deb75bfc84)
    * f1_dual_rev1: fix remaps
    -disable JTAG to free PA15, PB3, PB4
    -use SPI3 for EGT chips without remaping
2023-04-27 f1_dual_rev1: update ADC, measure Un_sense, avoid clamping
    (cherry picked from commit 26f12766968a1999e1f12e06720ecbc334a91add)
2023-04-29 f1_dual_rev1: update ADC, measure Un_sense, avoid clamping (#244)
    (cherry picked from commit 26f12766968a1999e1f12e06720ecbc334a91add)
2023-05-03 Rev 1pwm (#242)
    * f1_dual_rev1: fix analog aux output PWM definitions
    (cherry picked from commit 50e346dfcb9f223c6e0ee6cdc700cb376b536834)
    * fix pwm definitions
    (cherry picked from commit ce9e69b997290bbd7abcfe5af2926b1d556070cf)
    ---------
2023-05-03 indication: advanced indication with per-channel status led
    (cherry picked from commit b486dfe682622c9835cf00457834cebf6e34da2f)
2023-05-03 auxout: no need to invert PWM signal in software
2023-05-03 f1_dual_rev1: two TS serial ports: primary over BT, secondary over J3
2023-05-03 TS: report Nernst AC too, convert Nernst voltages to uint16
2023-05-03 livedata: temp is now packed int16
2023-05-29 livedata: temp is now packed int16 (#250)
2023-05-29 dual-rev1 Secondary uart settings (#247)
    * f1_dual_rev1: secondary TS port (BT)
    * f1_dual_rev1: two TS serial ports: primary over BT, secondary over J3
    ---------
2023-05-29 f1_dual_rev1: fix SPI1 remap
    (cherry picked from commit 38037e8b46ea4f9c2dd370560e6138ed35ade2f7)
2023-05-29 f1_dual_rev1: fix LD file
    (cherry picked from commit e9c0a26692d5f7bd8c0f1c46a2fd9b74edd223bf)
2023-05-29 lambda: getPhy for LSU ADV
    (cherry picked from commit dd3e3bf0d30c388ae3f19f3066cc91632b28f5d5)
2023-05-29 f1_port: handle MFS errors
    (cherry picked from commit b23b04edf24fabfd99461e7ca38ea165836645e6)
2023-05-29 max3185x: support also max31856 (#253)
    (cherry picked from commit 703985dc709afad2df0ff69d929751894da51b34)
2023-05-29 OpenBLT: extract common code for f1 boards (#255)
    (cherry picked from commit b892ed7520b20f00f1dbae88001798453a5bb07d)
2023-05-29 Sample script to flash using OpenBLT over CAN (#257)
    (cherry picked from commit 4c877b63e44966f5373c264a3c82556ac9883761)
2023-05-29 ts: support reset and reset to OpenBLT commands
    (cherry picked from commit 2f2fca401d7dc9a29e806013efec4d41570dd613)
2023-05-29 f1_dual_rev1: two TS serial ports: primary over BT, secondary over J3
    (cherry picked from commit 2fe5891f3e4d09d5feef2541ee19fc589d04eafd)
2023-05-29 f1_common: fix MFS flash allocation for STM32F103RCT6 used on dual_rev1
    (cherry picked from commit 258d33e8a7b79846afd4e0db791d87476b9d2041)
2023-05-29 f1_common: fix MFS flash allocation for STM32F103RCT6 used on dual_rev1 (#260)
    (cherry picked from commit 258d33e8a7b79846afd4e0db791d87476b9d2041)
2023-05-29 f1_dual_rev1: OpenBLT (#261)
    (cherry picked from commit 790de260f6e335a22737bb7d17d82687e620c838)
2023-05-29 pump_dac: implement GetPumpOutputDuty() for DAC output
    (cherry picked from commit 4ab46ce6c48f3a7fe9ad68e4254ac38b2845c872)
2023-06-02 TunerStudio: cleanup (#263)
2023-06-07 missed include
2023-06-07 pump_dac: implement GetPumpOutputDuty() for DAC output (#265)
    (cherry picked from commit 4ab46ce6c48f3a7fe9ad68e4254ac38b2845c872)
2023-06-11 OpenBLT reset functionality (#259)
    * ts: support reset and reset to OpenBLT commands
    (cherry picked from commit 2f2fca401d7dc9a29e806013efec4d41570dd613)
    * f1_xxx: ini: reset commands
    (cherry picked from commit 628994ba0a70901edb9b59360646aa195b3307cf)
    * typo
    * f1_xxx: ini: update signature
2023-06-11 f1_dual_rev1: debug and no-bootloader build helper
2023-06-15 f1_dual_rev1: debug and no-bootloader build helper (#266)
2023-06-15 OpenBLT: shared params between BL and main FW (#268)
2023-06-15 Include elf files to deliver
2023-06-21 extract sampling class
2023-06-21 heater uses sampling class
2023-06-22 f1_dual_rev1: no need in GD32 hack as rev1 use original STM32 (#269)
2023-06-23 class-ify HeaterController
2023-06-23 cycle
2023-06-23 add gtest
2023-06-23 test ci
2023-07-15 explicit struct fields
2023-07-15 unused includes
2023-07-22 unused includes (#274)
2023-08-09 bugfix: adding brackets for proper Operator Precedence
2023-08-09 stub some tests
2023-08-09 extract mk
2023-08-09 extract sampling thread
2023-08-09 stub enough for tests to build?
2023-08-09 dc sampler test
2023-08-09 accurate comment
2023-08-21 let's have gcc help us
2023-11-04 let's have gcc help us (#278)
2023-11-12 only reboot one controller at a time
2023-11-13 extract heater class declaration
2023-11-13 split heater thread and heater logic
2023-11-13 tests for heater output
2023-11-13 test heater state machine
2023-11-13 LSU ADV getPhi
2023-11-14 Fix reset to DFU command
2023-11-14 f1_dual_rev1: fix Heater vs Battery naming mess
2023-11-14 fix f1_dual_rev1
2023-11-15 fresh lib
2023-11-15 heater_control: do not preheat on low voltages
2023-11-15 fresh 042 for BL updater
2023-11-16 EOL in build yaml
2023-11-16 add timer class
2023-11-16 heater uses timers
2023-11-16 heater_control: do not preheat on low voltages (#286)
2023-11-16 fresh lib (#290)
2023-11-16 cherry-pick timer from ECU and use it for sequencing logic (#289)
    * enable timestamp api
    * add timer class
    * use unsigned integer for timestamps
    * heater uses timers
    * timer mocking and test adjustment
2023-11-16 auto-heat after 5 seconds of no CAN command #194
2023-11-16 fix it more
2023-11-18 stray returns?
2023-11-18 avoid NaN in case of zero battery voltage
2023-11-18 avoid 64 bit divide (!) exploding binary size
2023-11-19 heater: shortcut if sensor is hot enougth
2023-11-20 avoid 64 bit divide (!) exploding binary size fixing unit tests
2023-11-20 heater: 5 sec stabilization time after switching to closed loop
    LSU4.2 falls to Underheated state right after switch to closed loop
    due to rise of sensorEsr (due to applied pump current?)
2023-11-20 sampling, heater: fix Battery vs Heater naming mess
2023-11-23 conditionally compile TS as it's a memory hog
2023-11-23 Conditional compile ts (#298)
    * conditionally compile TS as it's a memory hog
    * naming so dumps are easier to read
2023-11-23 an undisclosed source says these parameters are better #296
2023-11-23 set valid bit only when nernst voltage is well controlled
2023-11-23 update F0 build outputs since it's in a good state
2023-11-23 F0 doesn't need UART
2023-12-03 TS_ENABLED vs ENABLE_TS: fix mess (#301)
    board.mk defines ENABLE_TS for Makefile
    while Makefile defines TS_ENABLED for compiled code.
    Use TS_ENABLED in main.cpp
2023-12-06 making TX period available since downstream wants to multiply it by two (#302)
2023-12-10 Gain vs loss confusion (#304)
2024-03-11 allow manual fw runs
2024-03-23 Fix paranoid check
2024-04-24 Typo in dac.h fix #308
2024-04-24 Typo in dac.h fix #308 (#315)
2024-04-25 report TX error condition with special LED state #316
2024-06-26 always use the new pump start logic
2024-06-26 revise comment
2024-09-25 better check lambda validity (#321)
2024-09-25 safer comparison of CAN frame size
2024-09-25 cleanup
2025-01-23 fdcan
2025-01-23 fix uart debug
2025-01-24 extract pump control pid config
2025-01-24 support having 4 pumps
2025-01-24 don't include hal
2025-01-24 include order
2025-01-24 sizeof instead of magic number
2025-01-24 why was LIN enabled...?
2025-01-24 bump ChibiOS to stable release, and update F0 configs
2025-01-24 F1 halconf update
2025-01-24 turn stuff off so the bootloader fits 😬
2025-01-24 temporarily remove F1 from CI
2025-01-27 max3185x: new SPI API
2025-01-27 PID: convert periodMs to S
2025-01-27 period in seconds (but prefer multiply over divide)
2025-01-28 enable WFI
2025-01-28 correct heater thread channel numbers
2025-01-28 complementary pump DAC outputs
2025-01-29 frequency note
2025-01-31 allow using complementary pins for pump dac
2025-01-31 max3185x: improve chip type detection
2025-01-31 max3185x: more const
2025-01-31 max3185x: deinit SPI bus after use
2025-01-31 max3185x: start in proper state
2025-01-31 max3185x: simplify, fix negative values for max31856
2025-01-31 Max3185x update (#328)
    * max3185x: more const
    * max3185x: deinit SPI bus after use
    * max3185x: improve chip type detection
    * max3185x: no magic numbers
    * max3185x: check spi_txrx return value
    * max3185x: simplify, fix negative values for max31856
2025-02-04 Fix reset to DFU command
    (cherry picked from commit c5db29006819475441eb0cf37f887639d21852fe)
2025-02-19 plumb mcu temp
2025-03-05 format
2025-05-08 reviving GHA
2025-05-16 pid config pointer -> ref
2025-05-19 revert cantx stack causing overflow (#332)
2025-05-21 Define more bootloader OpCodes
2025-05-21 Use bitwise OR in EID definitions
2025-05-28 f0: ld file, 256 bytes is 0x100
2025-05-28 Revert "revert cantx stack causing overflow (#332)"
    This reverts commit 718b7715d811be739c195e8263f0b6f72413d7eb.
2025-05-28 implement async adc on F0
2025-06-02 Set DAC_HAS_MCR FALSE in STM32F1xx registry.
2025-06-19 c++20
2025-06-20 toggle ESR driver before starting sampling
2025-06-20 implement F1 async adc
2025-06-20 GHA is glitching, manual update :(
2025-07-11 mcutemp
2025-07-24 add more status states
2025-07-24 add a hacky knob for pump gain over CAN
2025-07-25 use signalI, not signal for ADC done callback
2025-07-25 lock / unlock in adcDoneCallback
2025-07-27 this is always defined, so the guard is a noop
2025-08-19 heater control comment
2025-08-21 static -> static inline
2025-08-22 avoid low supply voltage -> infinite duty
2025-08-22 bump f0 image
2025-10-02 fix typo
2025-10-13 read the correct byte for pump gain
2025-12-13 CAN RX: filter out not ours packets by WB_BL_HEADER
2025-12-13 CAN: support ping command
    Reply with board HW ID (strap pins defined), protocol version
    (RUSEFI_WIDEBAND_VERSION) and build date
2025-12-13 CAN: send calculated lambda even it is not valid
    We have Valid field that user should check.
2026-02-27 Comprehensive test of heater state machine
2026-03-22 update kicad & bom tweaks
2026-03-22 update LED PNs
2026-04-03 bump image
2026-04-10 avoid trying to heat when battery voltage is low
2026-04-10 format config
2026-04-10 format pump, heater
2026-04-10 exclude f1, cfg from formatting
2026-04-10 format CAN
2026-04-10 format sampling, lambda
